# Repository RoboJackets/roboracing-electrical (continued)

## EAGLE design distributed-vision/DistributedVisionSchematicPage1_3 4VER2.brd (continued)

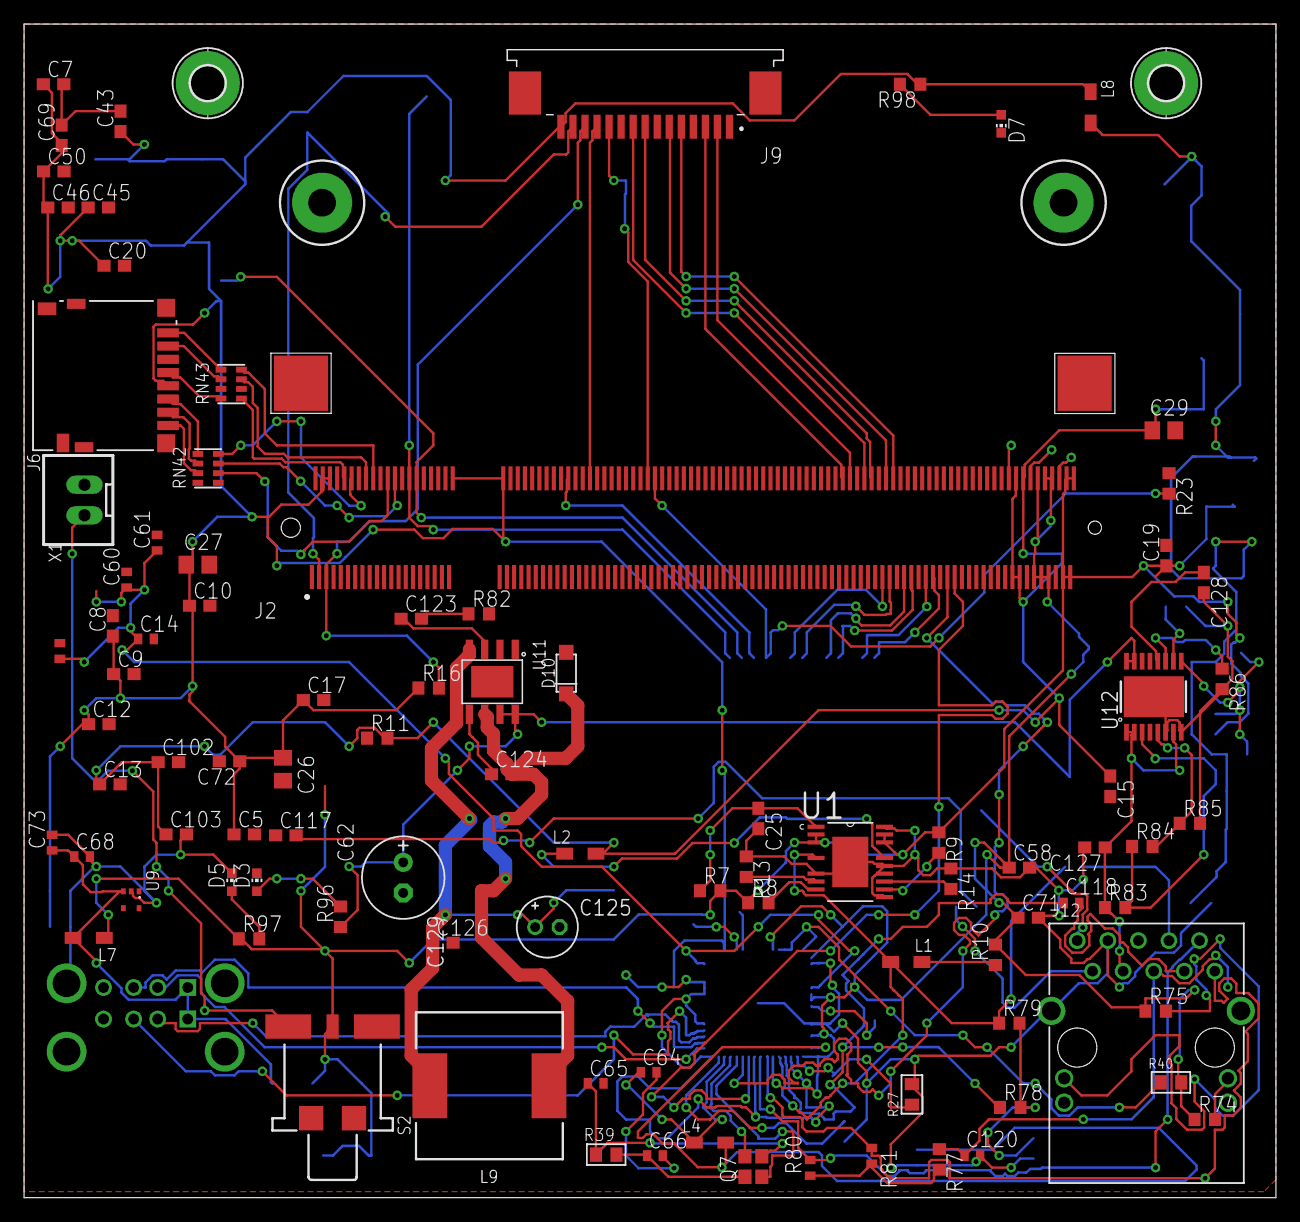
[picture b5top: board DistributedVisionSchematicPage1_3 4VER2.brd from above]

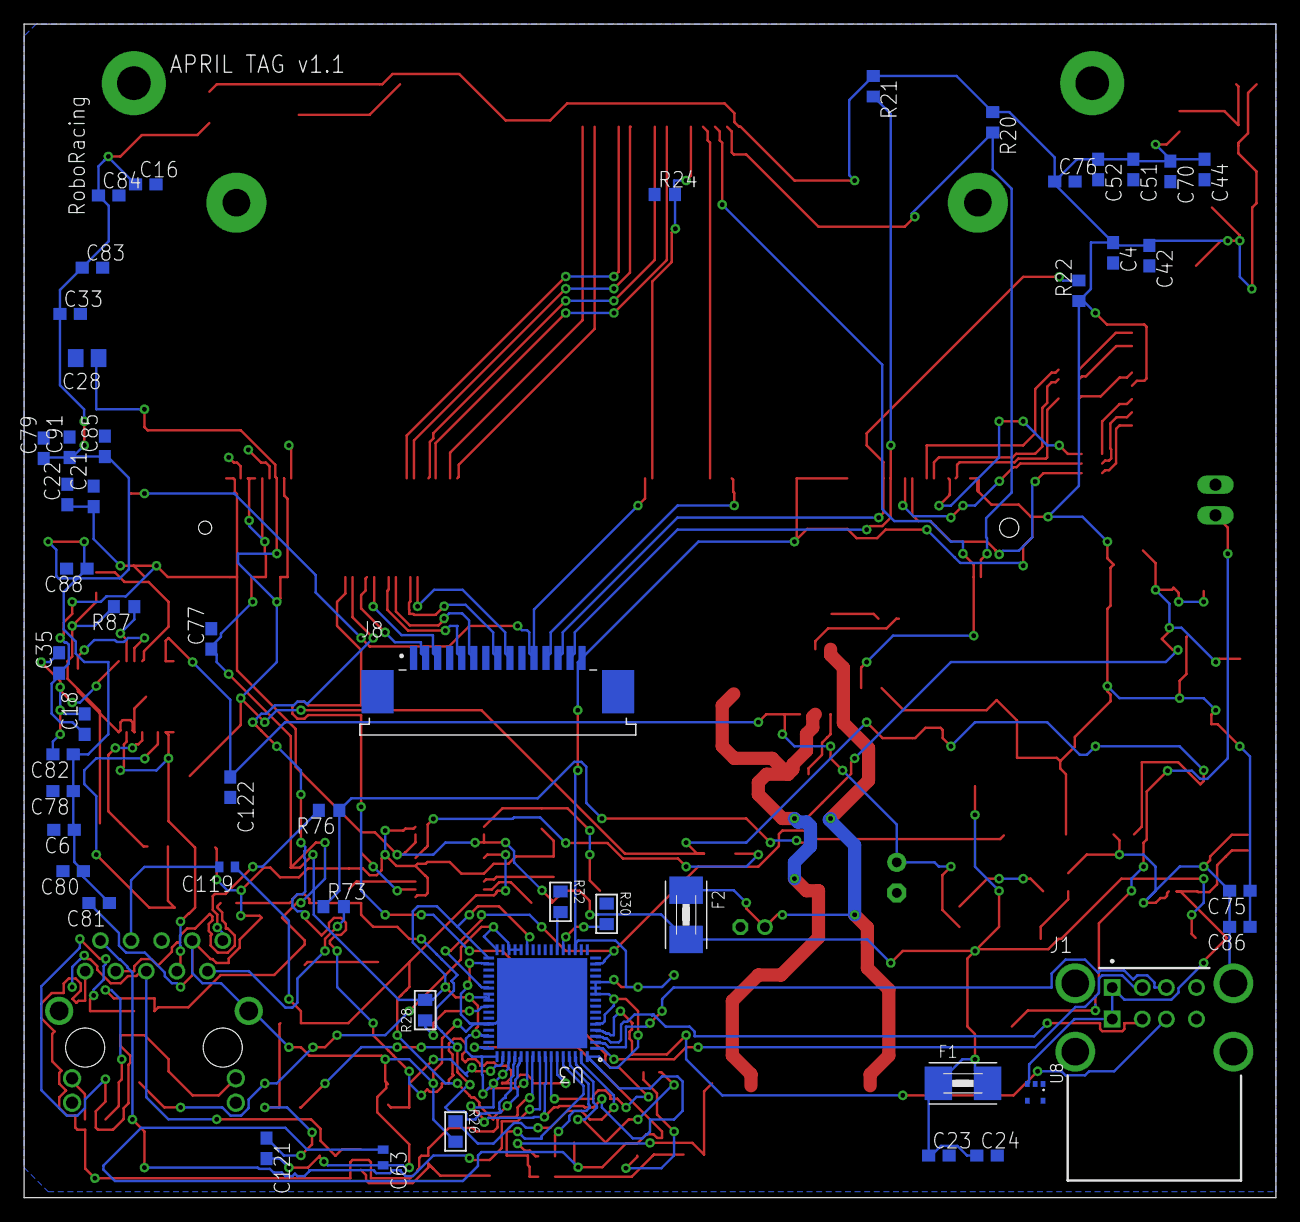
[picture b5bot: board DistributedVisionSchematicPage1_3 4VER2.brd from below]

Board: 2 copper layers, 104.0 x 97.5 mm, 147 parts (51 on the bottom side), 95 nets.

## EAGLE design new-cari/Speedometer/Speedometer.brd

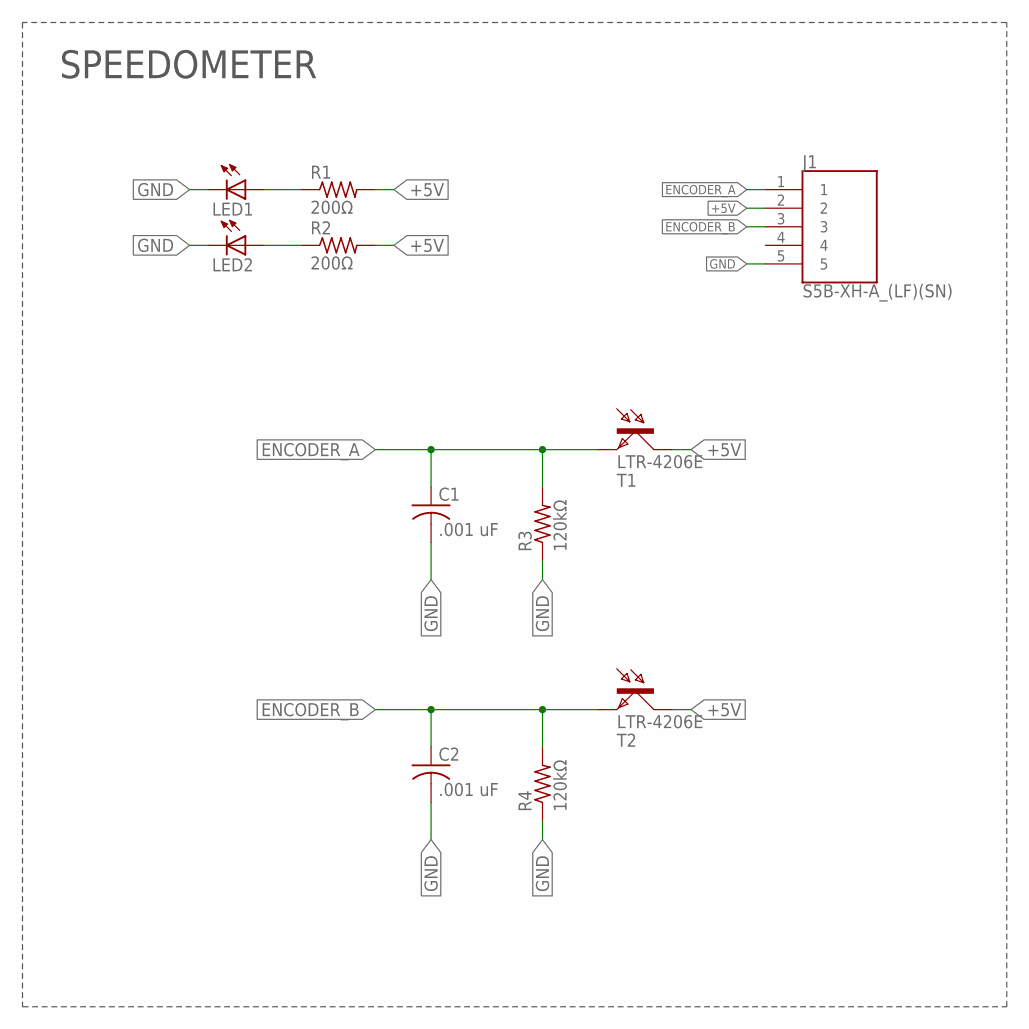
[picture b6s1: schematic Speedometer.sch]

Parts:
C1, C2: .001 uF; C0603
J1: S5B-XH-A_(LF)(SN); SHDR5W80P0X250_1X5_1490X1150X6
LED1, LED2: LED3MM
R1, R2: 200Ω; R0603
R3, R4: 120kΩ; R0603
T1, T2: LTR-4206E; BPX81

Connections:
+5V: J1.2, R1.2, R2.2, T1.C, T2.C
ENCODER_A: C1.1, J1.1, R3.2, T1.E
ENCODER_B: C2.1, J1.3, R4.2, T2.E
GND: C1.2, C2.2, J1.5, LED1.K (C), LED2.K (C), R3.1, R4.1
unnamed: LED1.A, R1.1
unnamed: LED2.A, R2.1

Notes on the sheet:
SPEEDOMETER

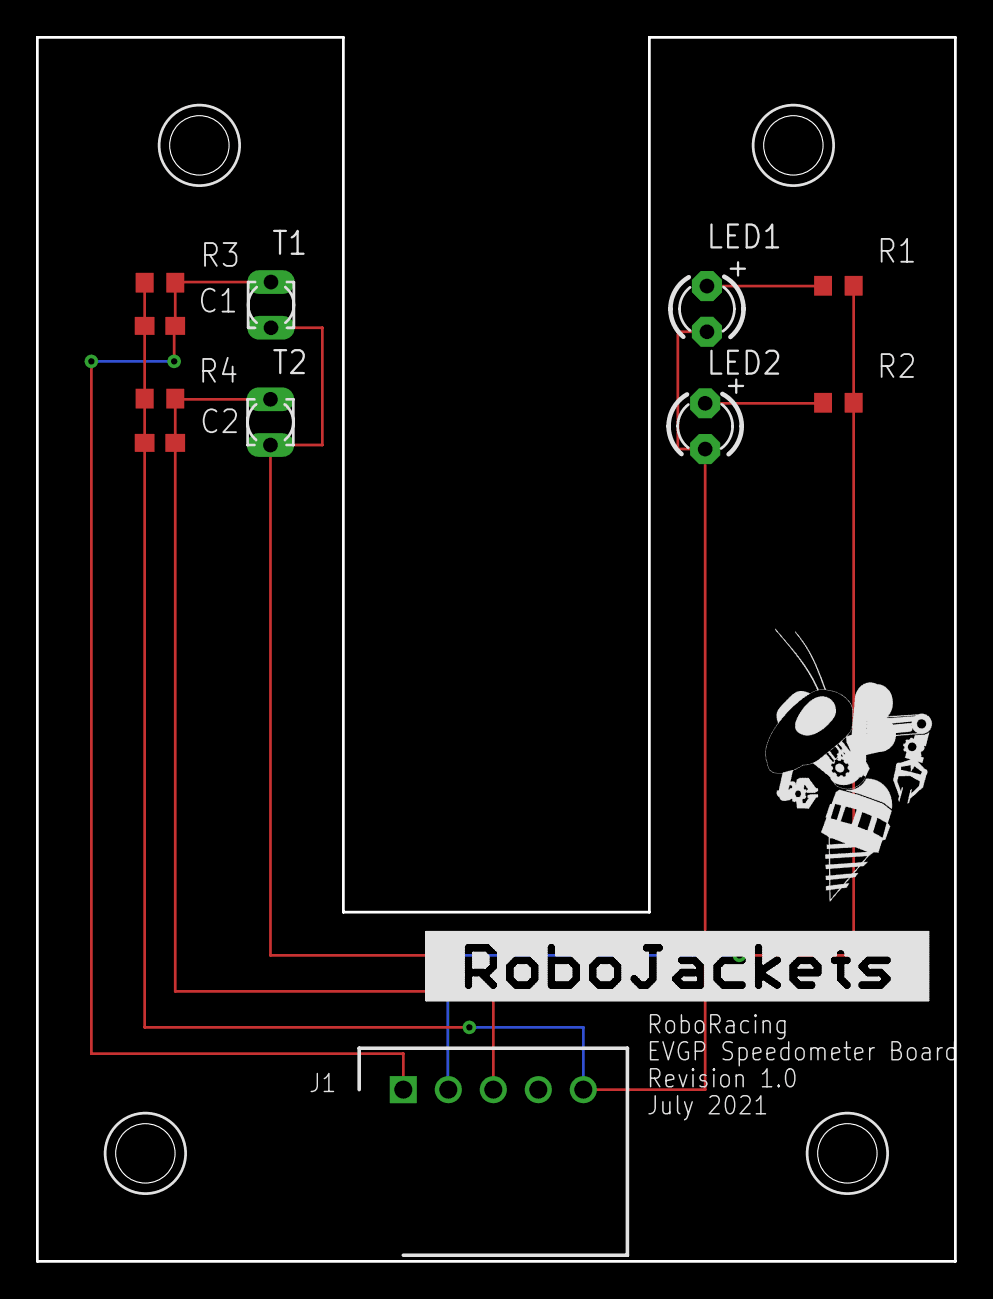
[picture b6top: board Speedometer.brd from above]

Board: 2 copper layers, 51.0 x 68.0 mm, 13 parts (0 on the bottom side), 6 nets.

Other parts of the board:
U$1: ROBOBUZZ_0.8X
U$2: ROBOJACKETS

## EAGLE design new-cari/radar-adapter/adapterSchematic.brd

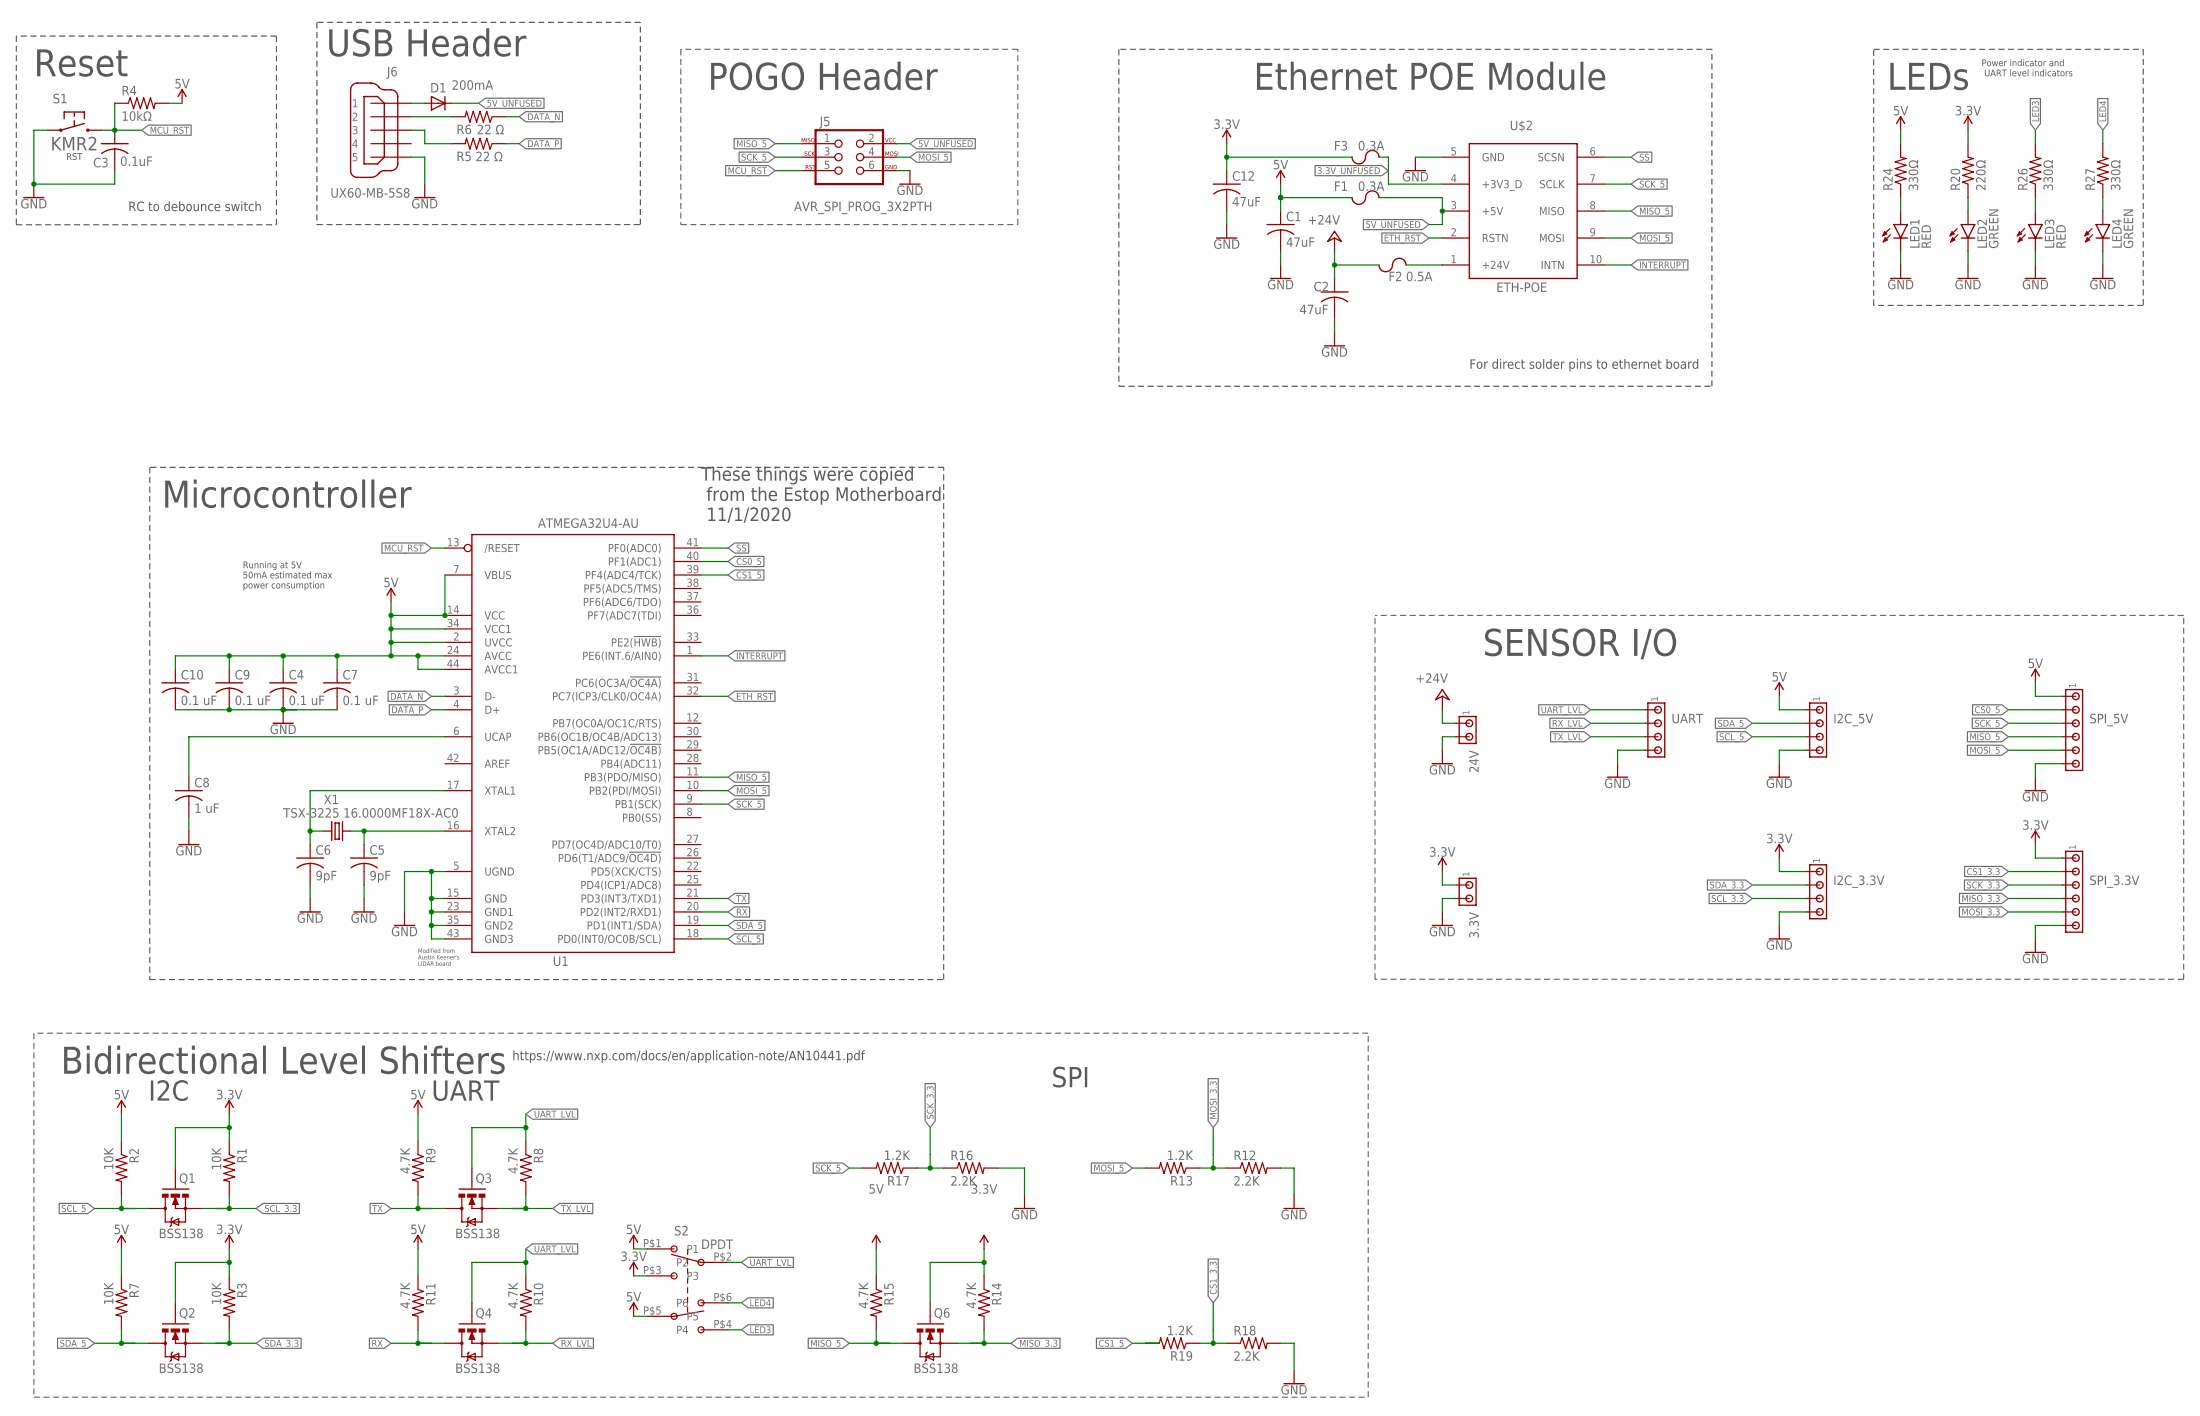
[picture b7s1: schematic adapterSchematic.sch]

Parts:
3.3V, 24V: MTA02-100; 10X02MTA
C1, C2, C12: 47uF; C1206
C3: 0.1uF; C0603
C4, C7, C9, C10: 0.1 uF; C0603
C5, C6: 9pF; C0603
C8: 1 uF; C0603
D1: 200mA; SOD323-R
F1, F3: 0.3A; F1206
F2: 0.5A; F1206
I2C_3.3V, I2C_5V: MTA04-100; 10X04MTA
J5: AVR_SPI_PROG_3X2PTH; 2X3
J6: UX60-MB-5S8
LED1, LED3: RED; CHIP-LED0603
LED2, LED4: GREEN; CHIP-LED0603
Q1, Q2, Q3, Q4, Q6: BSS138; SOT23-3
R1, R2, R3, R7: 10K; 0603-RES
R4: 10kΩ; R0603
R5, R6: 22 Ω; R0603
R8, R9, R10, R11, R14, R15: 4.7K; 0603-RES
R12, R16, R18: 2.2K; 0603-RES
R13, R17, R19: 1.2K; 0603-RES
R20: 220Ω; R0603
R24, R26, R27: 330Ω; R0603
S1: KMR2
SPI_3.3V, SPI_5V: MTA06-100; 10X06MTA
U1: ATMEGA32U4-AU; TQFP44
U$2: ETH-POE; HDRVR10W64P4000X254_2X5_1016X508X254B
U$4: DPDT_SLIDE_SWITCH
UART: MTA04-100; 10X04MTA
X1: TSX-3225 16.0000MF18X-AC0; XTAL-3.2X2.5

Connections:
3.3V: 3.3V.1, C12.1, F3.1, I2C_3.3V.1, Q1.1 (G), Q2.1 (G), Q6.1 (G), R1.1, R3.1, R14.1, R20.2, SPI_3.3V.1, U$4.P$3 (P3)
3.3V_UNFUSED: F3.2, U$2.4 (+3V3_D)
5V: C1.1, C4.1, C7.1, C9.1, C10.1, F1.1, I2C_5V.1, R2.1, R4.2, R7.1, R9.1, R11.1, R15.1, R24.2, SPI_5V.1, U1.2 (UVCC), U1.7 (VBUS), U1.14 (VCC), U1.24 (AVCC), U1.34 (VCC1), U1.44 (AVCC1), U$4.P$1 (P1), U$4.P$5 (P5)
5V_UNFUSED: D1.C, F1.2, J5.2, U$2.3 (+5V)
24V_UNFUSED: F2.2, U$2.1 (+24V)
+24V: 24V.1, C2.1, F2.1
CS0_5: SPI_5V.2, U1.40 (PF1(ADC1))
CS1_3.3: R18.1, R19.1, SPI_3.3V.2
CS1_5: R19.2, U1.39 (PF4(ADC4/TCK))
DATA_N: R6.1, U1.3 (D-)
DATA_P: R5.1, U1.4 (D+)
ETH_RST: U1.32 (PC7(ICP3/CLK0/OC4A)), U$2.2 (RSTN)
GND: 3.3V.2, 24V.2, C1.2, C2.2, C3.2, C4.2, C5.2, C6.2, C7.2, C8.2, C9.2, C10.2, C12.2, I2C_3.3V.4, I2C_5V.4, J5.6, J6.5, LED1.C, LED2.C, LED3.C, LED4.C, R12.2, R16.2, R18.2, S1.1.1 (1), S1.1.2 (1), SPI_3.3V.6, SPI_5V.6, U1.5 (UGND), U1.15 (GND), U1.23 (GND1), U1.35 (GND2), U1.43 (GND3), U$2.5 (GND), UART.4
INTERRUPT: U1.1 (PE6(INT.6/AIN0)), U$2.10 (INTN)
LED3: R26.2, U$4.P$4 (P4)
LED4: R27.2, U$4.P$6 (P6)
MCU_RST: C3.1, J5.5, R4.1, S1.2.1 (2), S1.2.2 (2), U1.13 (/RESET)
MISO_3.3: Q6.2 (S), R14.2, SPI_3.3V.4
MISO_5: J5.1, Q6.3 (D), R15.2, SPI_5V.4, U1.11 (PB3(PDO/MISO)), U$2.8 (MISO)
MOSI_3.3: R12.1, R13.1, SPI_3.3V.5
MOSI_5: J5.4, R13.2, SPI_5V.5, U1.10 (PB2(PDI/MOSI)), U$2.9 (MOSI)
unnamed: LED2.A, R20.1
unnamed: LED1.A, R24.1
unnamed: LED3.A, R26.1
unnamed: J6.2, R6.2
unnamed: D1.A, J6.1
unnamed: LED4.A, R27.1
unnamed: J6.3, R5.2
RX: Q4.3 (D), R11.2, U1.20 (PD2(INT2/RXD1))
RX_LVL: Q4.2 (S), R10.2, UART.2
SCK_3.3: R16.1, R17.1, SPI_3.3V.3
SCK_5: J5.3, R17.2, SPI_5V.3, U1.9 (PB1(SCK)), U$2.7 (SCLK)
SCL_3.3: I2C_3.3V.3, Q1.2 (S), R1.2
SCL_5: I2C_5V.3, Q1.3 (D), R2.2, U1.18 (PD0(INT0/OC0B/SCL))
SDA_3.3: I2C_3.3V.2, Q2.2 (S), R3.2
SDA_5: I2C_5V.2, Q2.3 (D), R7.2, U1.19 (PD1(INT1/SDA))
SS: U1.41 (PF0(ADC0)), U$2.6 (SCSN)
TX: Q3.3 (D), R9.2, U1.21 (PD3(INT3/TXD1))
TX_LVL: Q3.2 (S), R8.2, UART.3
UART_LVL: Q3.1 (G), Q4.1 (G), R8.1, R10.1, U$4.P$2 (P2), UART.1
UCAP: C8.1, U1.6 (UCAP)
XTAL1: C6.1, U1.17 (XTAL1), X1.1
XTAL2: C5.1, U1.16 (XTAL2), X1.3 (2)

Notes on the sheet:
Modified from Austin Keener's LIDAR board
Running at 5V 50mA estimated max power consumption
Microcontroller
Ethernet POE Module
For direct solder pins to ethernet board
RC to debounce switch
Reset
USB Header
POGO Header
SENSOR I/O
These things were copied from the Estop Motherboard 11/1/2020
Bidirectional Level Shifters
I2C
UART
SPI
Power indicator and UART level indicators
LEDs
https://www.nxp.com/docs/en/application-note/AN10441.pdf

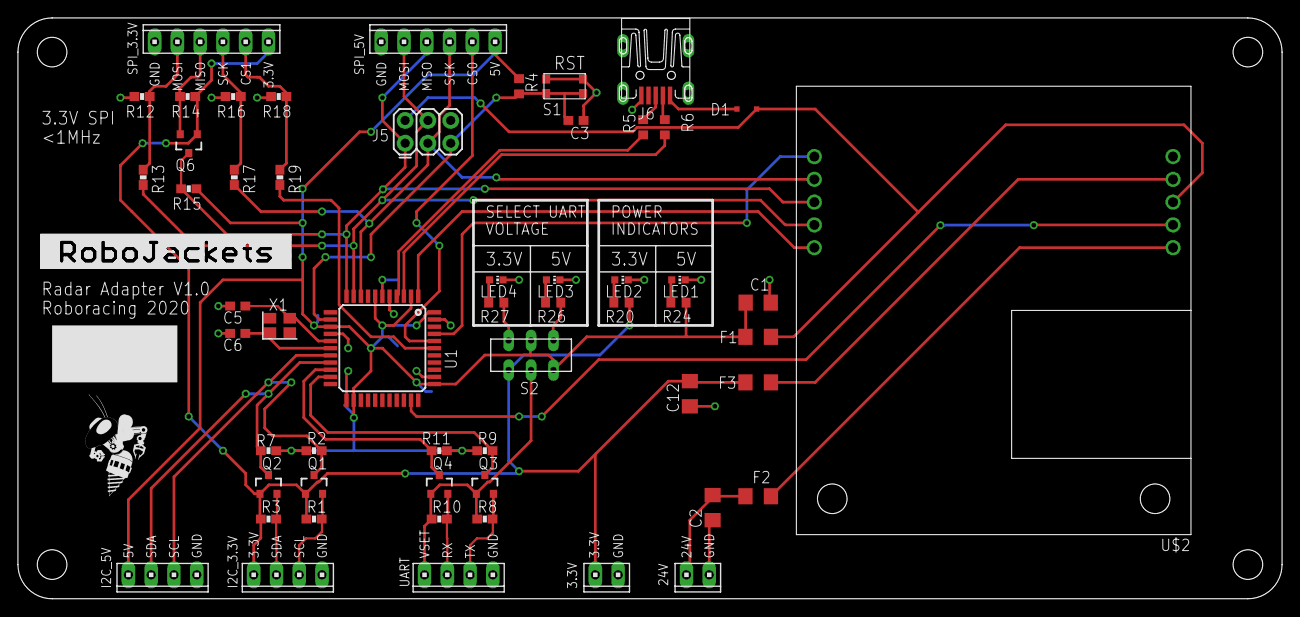
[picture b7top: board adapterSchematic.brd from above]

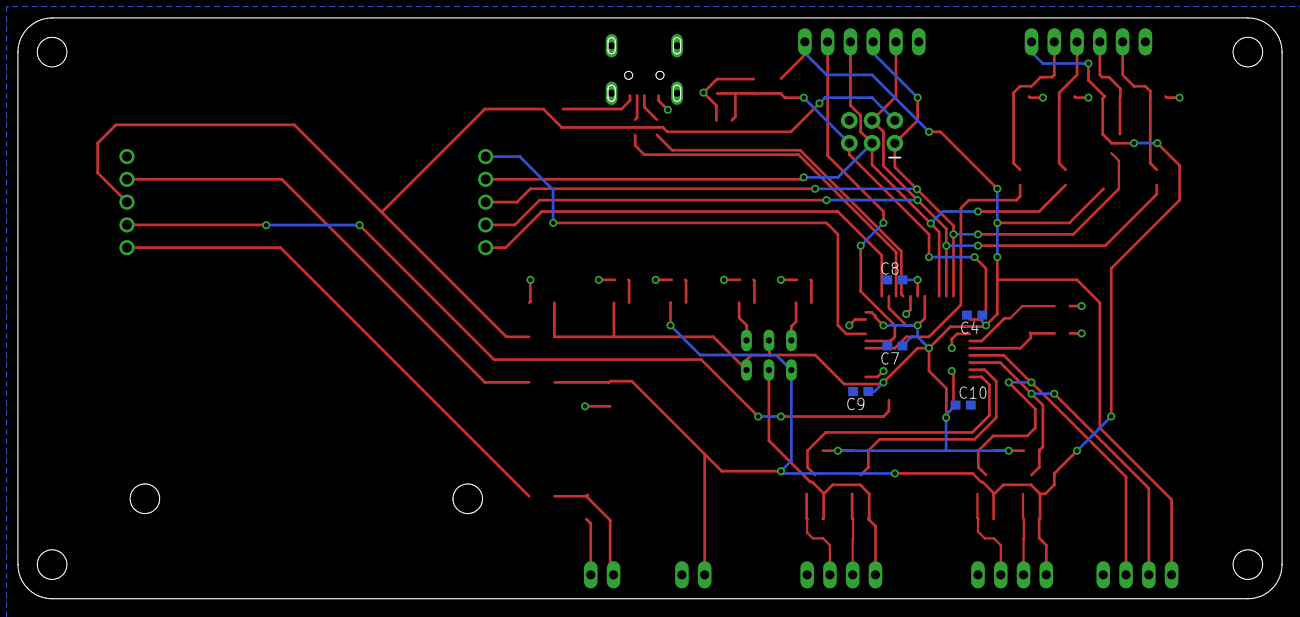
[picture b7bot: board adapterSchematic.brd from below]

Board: 2 copper layers, 141.0 x 64.8 mm, 63 parts (5 on the bottom side), 43 nets.

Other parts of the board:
U$1: ROBOBUZZ_0.6X
U$3: ROBOJACKETS

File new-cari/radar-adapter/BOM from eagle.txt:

Part	Value	Device	Package	Description	FUNCTION	PINS	POPULARITY	Vendor Part Number	description	Unit Quantity	Price
3.3V		MTA02-100	10X02MTA	AMP connector			5				
24V		MTA02-100	10X02MTA	AMP connector			5				
C1	10uF	C-USC1206	C1206	"CAPACITOR, American symbol"			24	478-10766-1-ND	CAP CER 10UF 10V X5R 0603	1	0.14
C2	10uF	C-USC1206	C1206	"CAPACITOR, American symbol"			24	478-10766-1-ND	CAP CER 10UF 10V X5R 0603	1	0.14
C3	0.1uF	C-USC0603	C0603	"CAPACITOR, American symbol"			37	1276-1006-1-ND	CAP CER 0.1UF 25V X7R 0603	1	0.1
C4	0.1 uF	C-USC0603	C0603	"CAPACITOR, American symbol"				1276-1006-1-ND	CAP CER 0.1UF 25V X7R 0603	1	0.1
C5	9pF	C-USC0603	C0603	"CAPACITOR, American symbol"				490-11483-1-ND	CAP CER 9PF 50V C0G/NP0 0603	1	0.12
C6	9pF	C-USC0603	C0603	"CAPACITOR, American symbol"				490-11483-1-ND	CAP CER 9PF 50V C0G/NP0 0603	1	0.12
C7	0.1 uF	C-USC0603	C0603	"CAPACITOR, American symbol"				1276-1006-1-ND	CAP CER 0.1UF 25V X7R 0603	1	0.1
C8	1 uF	C-USC0603	C0603	"CAPACITOR, American symbol"				1276-1102-1-ND	CAP CER 1UF 25V X5R 0603	1	0.1
C9	0.1 uF	C-USC0603	C0603	"CAPACITOR, American symbol"				1276-1006-1-ND	CAP CER 0.1UF 25V X7R 0603	1	0.1
C10	0.1 uF	C-USC0603	C0603	"CAPACITOR, American symbol"				1276-1006-1-ND	CAP CER 0.1UF 25V X7R 0603	1	0.1
C12	10uF	C-USC1206	C1206	"CAPACITOR, American symbol"			24	478-10766-1-ND	CAP CER 10UF 10V X5R 0603	1	0.14
D1	200mA	DIODE-SOD323-R	SOD323-R	DIODE				1727-3561-1-ND	DIODE SCHOTTKY 30V 200MA SOD323	1	0.21
F1	0.3A	CHIP_FUSE1206	F1206					F10984CT-ND	PTC RESET FUSE 24V 300MA 1206	1	1.12
F2	0.5A	CHIP_FUSE1206	F1206					F10984CT-ND	PTC RESET FUSE 24V 300MA 1206	1	1.12
F3	0.3A	CHIP_FUSE1206	F1206					F10984CT-ND	PTC RESET FUSE 24V 300MA 1206	1	1.12
I2C_3.3V		MTA04-100	10X04MTA	AMP connector			1				
I2C_5V		MTA04-100	10X04MTA	AMP connector			1				
J5	AVR_SPI_PROG_3X2PTH	AVR_SPI_PROG_3X2PTH	2X3	AVR ISP 6 Pin							
J6	UX60-MB-5S8	UX60-MB-5S8	UX60-MB-5S8	Mini USB Connector		5					
LED1	RED	LEDCHIP-LED0603	CHIP-LED0603	LED							
LED2	GREEN	LEDCHIP-LED0603	CHIP-LED0603	LED							
LED3	RED	LEDCHIP-LED0603	CHIP-LED0603	LED							
LED4	GREEN	LEDCHIP-LED0603	CHIP-LED0603	LED							
Q1	BSS138	MOSFET-NCHANNELSMD	SOT23-3								
Q2	BSS138	MOSFET-NCHANNELSMD	SOT23-3								
Q3	BSS138	MOSFET-NCHANNELSMD	SOT23-3								
Q4	BSS138	MOSFET-NCHANNELSMD	SOT23-3								
Q6	BSS138	MOSFET-NCHANNELSMD	SOT23-3								
R1	10K	RESISTOR0603-RES	0603-RES	Resistor							
R2	10K	RESISTOR0603-RES	0603-RES	Resistor							
R3	10K	RESISTOR0603-RES	0603-RES	Resistor							
R4	10kΩ	R-US_R0603	R0603	"RESISTOR, American symbol"							
R5	22 Ω	R-US_R0603	R0603	"RESISTOR, American symbol"							
R6	22 Ω	R-US_R0603	R0603	"RESISTOR, American symbol"							
R7	10K	RESISTOR0603-RES	0603-RES	Resistor							
R8	4.7K	RESISTOR0603-RES	0603-RES	Resistor							
R9	4.7K	RESISTOR0603-RES	0603-RES	Resistor							
R10	4.7K	RESISTOR0603-RES	0603-RES	Resistor							
R11	4.7K	RESISTOR0603-RES	0603-RES	Resistor							
R12	2.2K	RESISTOR0603-RES	0603-RES	Resistor							
R13	1.2K	RESISTOR0603-RES	0603-RES	Resistor							
R14	4.7K	RESISTOR0603-RES	0603-RES	Resistor							
R15	4.7K	RESISTOR0603-RES	0603-RES	Resistor							
R16	2.2K	RESISTOR0603-RES	0603-RES	Resistor							
R17	1.2K	RESISTOR0603-RES	0603-RES	Resistor							
R18	2.2K	RESISTOR0603-RES	0603-RES	Resistor							
R19	1.2K	RESISTOR0603-RES	0603-RES	Resistor							
R20	220Ω	R-US_R0603	R0603	"RESISTOR, American symbol"							
R24	330Ω	R-US_R0603	R0603	"RESISTOR, American symbol"							
R26	330Ω	R-US_R0603	R0603	"RESISTOR, American symbol"							
R27	330Ω	R-US_R0603	R0603	"RESISTOR, American symbol"							
S1	KMR2	KMR2	KMR2		RST						
SPI_3.3V		MTA06-100	10X06MTA	AMP connector			0				
SPI_5V		MTA06-100	10X06MTA	AMP connector			0				
U$2	ETH-POE	ETH-POE	HDRVR10W64P4000X254_2X5_1016X508X254B	POE							
U$4	DPDT_SLIDE_SWITCH	DPDT_SLIDE_SWITCH	DPDT_SLIDE_SWITCH								
U1	ATMEGA32U4-AU	ATMEGA32U4-AU	TQFP44	http://www.ladyada.net/library/eagle							
UART		MTA04-100	10X04MTA	AMP connector			1				
X1	TSX-3225 16.0000MF18X-AC0 	XTAL-3.2X2.5	XTAL-3.2X2.5

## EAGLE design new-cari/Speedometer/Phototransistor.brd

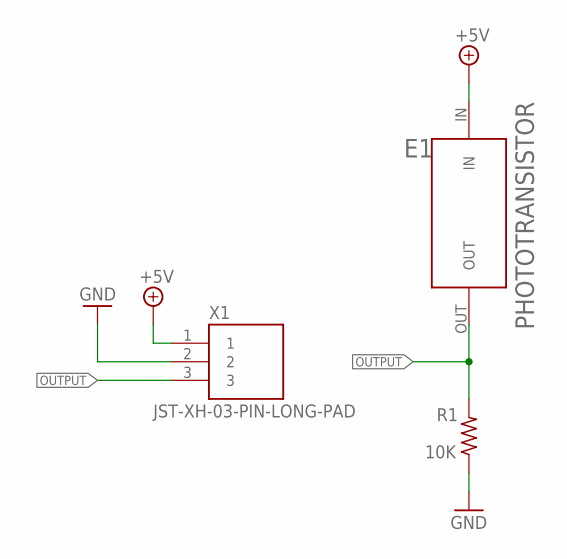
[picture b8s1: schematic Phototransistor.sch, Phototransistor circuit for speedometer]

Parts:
E1: PHOTOTRANSISTOR; STD_FP
R1: 10K; R0603
X1: JST-XH-03-PIN-LONG-PAD; JST-XH-03-PACKAGE-LONG-PAD

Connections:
+5V: E1.IN, X1.1
GND: R1.1, X1.2
OUTPUT: E1.OUT, R1.2, X1.3

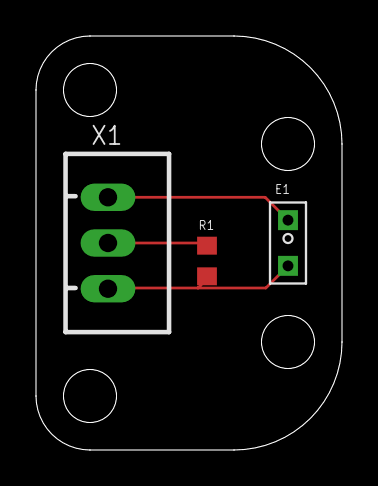
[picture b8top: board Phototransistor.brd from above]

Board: 2 copper layers, 17.0 x 23.0 mm, 3 parts (0 on the bottom side), 3 nets.

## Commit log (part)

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2019-11-25 Updated board and schematic
    Changed encoder data to interrupt pin.
2019-11-25 Completed Routing for reivew
2019-11-25 Silkscreen and via adjustment
2019-11-25 Added constellated vias
2019-11-25 Added Status LED
2019-11-26 changed device led name
2019-11-26 Added indicator LED
2019-11-26 design review changes
2019-11-26 I'm not actually sure if anything has changed
2019-11-26 fixed some routing widths, added fuse values, etc
2019-11-26 fixed drc errors
2019-11-26 Changed file name and added schematic border
2019-11-26 Changed the library name, added 555 to library, implemented into both 'normal' and 'led' boards
2019-11-28 Board and CAD Updates
    -Made changes recommended in informal design review
    -Exported Board file to Inventor and continued CAD assembly
2019-12-01 Added Ethernet Poe Board CAD
2019-12-01 Continue updateding board and schematic with design review changes
2019-12-02 Mounting
    -Added CAD files for nearly entire assembly
    -Widened plastic mounting bracket
    -Added supporting ribs
    -Fileted everything to make it pretty
    -Fixed hole pattern in eth-poe
    -Fixed hole pattern in lower-right steering board mounting hole
2019-12-02 Fixed eth-poe footprint
    moved the holes on the ethernet-poe footprint down and in by 1mm in both the x and y directions, to match the existing state of the board
2019-12-02 Replaced Eth PoE board
    Hopefully now using the updated library w/ proper mounting hole locations
2019-12-02 Updated ethernet footprint
2019-12-02 Added holes under PoE mounting holes
2019-12-02 Fixed label style
2019-12-02 Board cleanup
    More room for zipties, cleaner routing, moved RC outline to bottom layer (where it will be placed)
2019-12-03 Receiver now completely under board
2019-12-03 Updated changes from design review
2019-12-03 Added second status LED
2019-12-03 Updated design review changes
2019-12-03 Made small silkscreen changes, moved usb to edge
2019-12-03 Turned off thermals
2019-12-03 Added documentation on tDocu layer
2019-12-03 changed name of Estop_Daughterboard folder
2019-12-03 test folder added
2019-12-03 moved test folder into new-cari
2019-12-03 changed readme
2019-12-03 Finished routing new connecters
2019-12-03 Fixed USB routing widths
2019-12-04 made some minor a e s t h e t i c tweaks to the board layout
2019-12-07 added crystal to BOM
2019-12-30 making sure right part number in sheet
2020-01-05 Fall design review changes pt1
2020-01-07 Fall design review changes pt3
2020-01-07 moved the estop_motherboard file from Estop_daugherboard to Estop_Daugherboard
2020-01-07 Some design review changes
2020-01-08 Design review changes 1
2020-01-08 Design review changes 2
2020-01-08 Button implemented in hardware through AND gates
2020-01-09 Post-Design Review Board Changes
2020-01-09 Edited ethernet library part to have 44.5mm width and 40.64mm spacing to allow mating to 0.1in headers
2020-01-09 passing DRC now
2020-01-09 Made some minor adjustments
2020-01-09 Fixed supply symbol for 5V input
2020-01-10 Label changes to schematic
    Also trying to add another pin to the reciever so we can see when it's plugged in
2020-01-10 Button changed to NO w/ pulldown resistor, inputs to MCU changed to IN signals
2020-01-10 Brake_en moved to PWM pin on mcu
2020-01-10 Update from review 2
2020-01-10 Fixed labels and orientation of RJ Logo
2020-01-11 Added digikey part number attribute to most parts
2020-01-12 test
2020-01-12 added CAM file
2020-01-12 Added fuse current rating estimation
    Check design review doc for potential concerns
2020-01-14 Create control_board_3.3_parts.csv
    Rearranged some column orders on the BOM
2020-01-14 Removed Pink LED
    Sorry Kyle
2020-01-14 did absolutely nothing
2020-01-14 Update control_board_3.3_parts.csv
    Added quantity per board column
2020-01-14 Create sedani_chassis_control_2020-01-14.zip
    Made CAM file
2020-01-14 added throttle and switch connectors
2020-01-14 Updated resistive bridge with cap to gnd
2020-01-14 Cleaned up schematic and board
2020-01-18 added new ethernet jack part
2020-01-18 changed ethernet jack and rerouted
2020-01-20 removed arduino folder
2020-02-18 did an inventory
2020-02-19 finished to order list
2020-03-29 Added LED Cube personal project
2020-03-29 Removed extraneous file
2020-04-06 Replaced Non-Assmann VGA connector with TE one
    Look it's not pretty but it's 2 AM routing. It'll do the job.
2020-04-06 fixed readme
2020-04-06 Improved documentation on schematic
2020-04-13 Updated SCNN pin
2020-04-13 Updated CS_ETH pin
2020-04-13 Fixed USB to ground
2020-05-24 Updating description of LDO
2020-05-25 Added more parts to library, cleaned up board and schematic
2020-05-26 Added termination of ethernet taps
2020-06-15 Updated symbols to Style Guide standards
2020-06-23 Updated to Style Guide Standards
2020-06-26 First routing and layout pass completed.
2020-06-26 Updated poe library with oscillator
2020-06-27 Updated Steering library to style guide standards
2020-06-28 Updated board_outline library to style guide standards
2020-06-28 Updated EVGP_Estop_Motherboard library to style guide standards
2020-06-28 Updated neopixel_board library to style guide standards
2020-06-28 Updated WIZ850io library to style guide standards
2020-07-07 updates
    -added grounded mounting holes
    - added ground and stich capacitor for SPI line return current
    - added some polygons
    - fixed several DRC errors
2020-07-08 Actually finished changes for eFuse schematic
2020-07-11 routing for efuse
2020-07-12 Pre Review Commit, Completed Routing
2020-07-12 added DRC
2020-07-12 Made drc compliant
2020-07-25 Began design review changes
2020-08-03 post design review routing updates
    replaced 5V DC/DC converter catch diode
    routed Wiznet LEDs
    added thermal pads to efuse and DC/DC converters
2020-08-07 added top board with wiznet port
2020-08-24 Changed capacitor for load
2020-08-24 Updated more values based on availability
2020-09-19 Revert "Delete ethernet_poe.lbr to resolve conflict"
    This reverts commit ef95645cfb66f80d5ac58dd1acb75e853ce7e5ff.
2020-10-11 Setup initial library
2020-10-15 Made v2.1, updated initial problems on library, sch
2020-10-18 Cleaned up some labels
2020-10-18 Library Contains SP3003-02
    Created the SP3003-02 part in Eagle.
2020-10-25 Added ESD224 part to the library
2020-10-25 Added DKPN and implemented stylistic fixes
2020-11-01 copied over circuit blocks from Estop motherboard
2020-11-02 got rid of empty project file
2020-11-07 Committing TPS70625DBVR Part
    Finished Part.
2020-11-07 Committed LM26420XMH Part.
2020-11-08 Added library with USB and HDMI Control
2020-11-08 Sylistic change in Symbol for LM26420XMH
2020-11-08 Committed XS10 (Compute Header)
2020-11-08 Committed LAN9513-JZX
2020-11-08 Began raspberry pi compute
2020-11-09 Finished Raspberry Pi Compute
2020-11-17 Added headers to board and rough board layout.
2020-11-22 Added bidirectional level shifters for 3.3v SPI and I2C connectivity
2020-11-22 Updated Capacitors/Resistors
2020-11-23 repositioned some headers
2020-12-04 Finished board changes
2020-12-04 Removed old manufacturing files
2021-01-08 Fixed Silkscreen, added header pinout, misc touchups
2021-01-16 Finished Page 3, Re-working Page 1
2021-01-17 more fixes
2021-01-18 passing drc except for header errors
2021-01-22 Disb Vision Library Edit/Schematic Update
    Edited Pins 4,6,10,12,14,16,18,22,24 to SDX_ for MicroSD
    Finish Micro_SD part of Schematic on Pg 1
    Replaced BJT with JP1 on Pg 3
2021-01-23 Corrected FB1 Label Issue
2021-01-24 Added Page 2 of StereoPi Schematic
2021-01-31 Combined all Schematic Pages
    Fixed some Capacitor/Resistor Values
    Began integrating POE
2021-02-01 moved usb, trace under label, and stray line on silkscreen
2021-02-07 Cleaning up Schematic
2021-02-07 Integrated PoE
2021-02-14 Added schematic files for speedometer
2021-02-21 Cleaned up Schematic/Worked on Board
2021-03-07 added components etc to BOM
2021-03-07 with BOM
2021-03-21 Board/Schematic Update
2021-03-21 Schematic/Board
2021-04-26 This is some firmware that plots the radar position and velocity data
2021-05-15 Version 3
2021-05-15 Joe Cleanup Schematic
2021-05-16 Updated Values in DisbVision sch
2021-05-16 Routed Board Based off Schematic Changes
2021-05-16 Updated Gerber
2021-05-17 Added pick and place
2021-05-17 BOM/PnP Changes
2021-07-11 Created Speedometer board
    Created board file and removed other unused files
2021-07-11 Added RoboBuzz/RoboJackets symbols on board
2021-07-14 Updated board and gerber files
2021-10-24 Made CSV so git trackable
2021-10-24 Cleanup for merge
2021-10-24 Restored deleted files
2021-10-24 Updates readme
2021-10-24 Remove DS_Store
2021-12-05 Added battery monitor schematic and board layout
    Work in progress
2021-12-05 Fix R1 value
2021-12-12 First Draft Done!
2022-01-16 E-stop-radio board created (Rough)
    Still in the process of rearranging the components.
2022-01-18 Steering Schematic Draft 1
2022-01-21 Switched out old Nucleo Header with updated one that has Morpho Connectors Integrated
2022-01-22 Integrated new header symbols and updated power circuitry on steering schematic
2022-01-23 Create DESCRIPTION
2022-01-23 Create QSH-030-01-X-D-A-XX.lbr
    Added library for LCD female connector
2022-01-23 Updated power circuitry
2022-01-24 Added 12V to 5V power circuit and LCD connector to schematic
    Started to assign pins between the LCD connector and the nucleo header pins
2022-01-28 with copy files
2022-01-29 with headers and TVS
2022-01-30 Committed for Archie/Advaith
2022-01-31 eStopV2 Rough Draft Complete
    Optimization is still needed
2022-02-01 Finished Rough Draft for Schematic Review
    Not updated with changes suggested during schematic review
2022-02-04 Implemented changes from schematic review
    LED Connector and Power Circuitry still needs to be updated in schematic
2022-02-04 Steering Schematic Updated After Internal Design Review
2022-02-05 Adjusted some placement
2022-02-05 Started routing the board
    LED connector still not completed
2022-02-13 Completed routing for v1.0
    Removed LED connector and ready for design review
2022-02-20 Uploading Library and Eagle Schematic
2022-02-20 Cleaned up schematic and board
    Removed unused library and updated out of stock/not sold components
2022-02-23 Cleaned up
2022-02-23 Board Cleanup
2022-02-24 Cleaned up brd
2022-02-26 Schematic Design
    Schematic Design updated and components changed
2022-02-27 Footprint Update
    Updated Footprints for receiver and RGB light
2022-03-14 Moved Files to Correct Branch
    moved files from ecosystem to john branch
2022-03-14 Manual Board Update
    Ran DRC on board and fixed errors
2022-03-15 Gerber File
    Gerber File added to folder
2022-03-15 Board update
    Updates silkscreen and trace widths
2022-03-15 cam data and silkscreen
    Generated CAM data and updated silkscreen
2022-04-06 Fixed Gerber Files
    Created new Gerber File for manual Board
2022-11-23 Updated Board
    Changed Transeiver Holes and Spacing and RGB LED holes and spacing
2023-11-12 Add start of STM schematic
2023-11-12 Remove unnecessary KiCad files
2024-01-23 removed unnecessary parts and imported from eagle to kicad
2024-04-07 Added some changes to CAN header board for Nucleo
2024-04-12 Finished CAN to Ethernet PCB Header for Nucleo
2024-04-12 Added some RoboJackets theming
2024-04-16 Completed PCBs for 2024
